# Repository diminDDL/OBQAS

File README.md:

# OBQAS
Open Battery Quantification and Analysis System

A high efficiency high power imax alternative.

Features include:

* up to 5 Li-ion cells (22 Vout max)

Supported battery types:
* Li-ion (with balancing)
* Ni-mh
* Ni-cd
* Pb
* More...

Ratings:
* Maximum output voltage - 22V
* Maximum charging current - 5A
* Maximum charging power: ~100W

Discharge:
* Maximum input voltage - 22V
* Maximum discharging current - 3A (up to 5A with a better MOSFET)
* Maximum discharging power: ~75W

Input voltage:
12-24V

Topology:
buck-boost synchronous (TPS55288)

Additional features:
20x4 display with encoder
USB-C for data logging and remote control/outputs 5V 1A
SD card holds configuration parameters/standalone data logging
Thermocopule for battery monitoring
ESP32 - WiFI/BLE

### Pictures

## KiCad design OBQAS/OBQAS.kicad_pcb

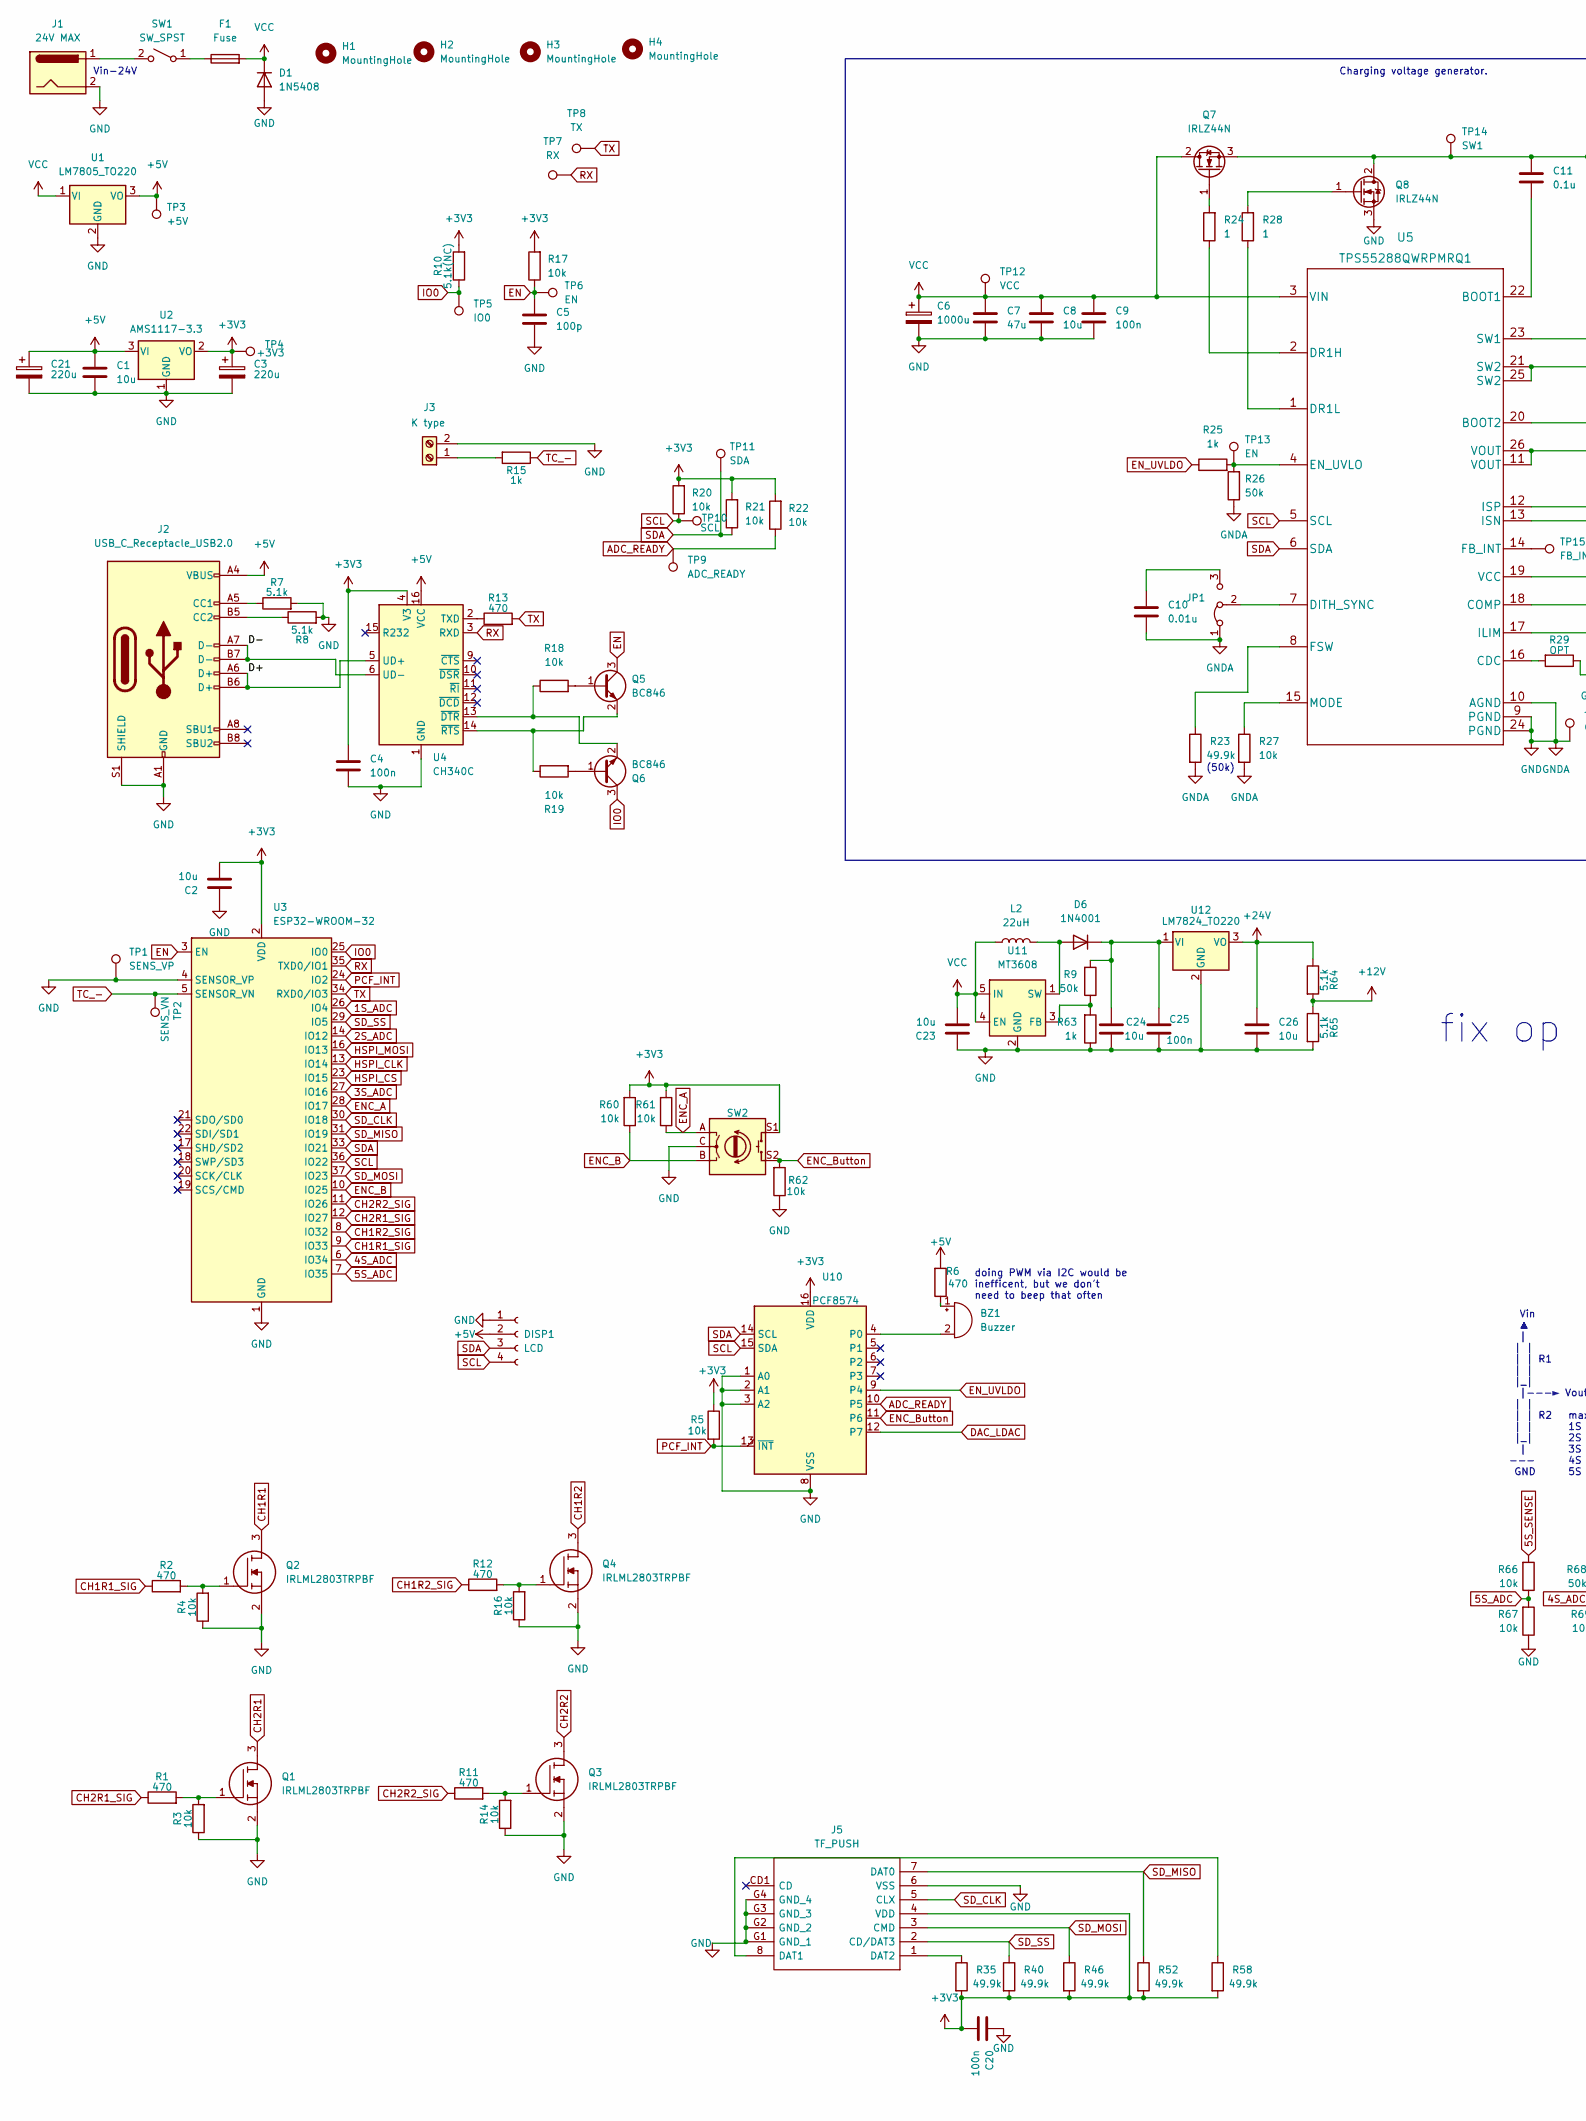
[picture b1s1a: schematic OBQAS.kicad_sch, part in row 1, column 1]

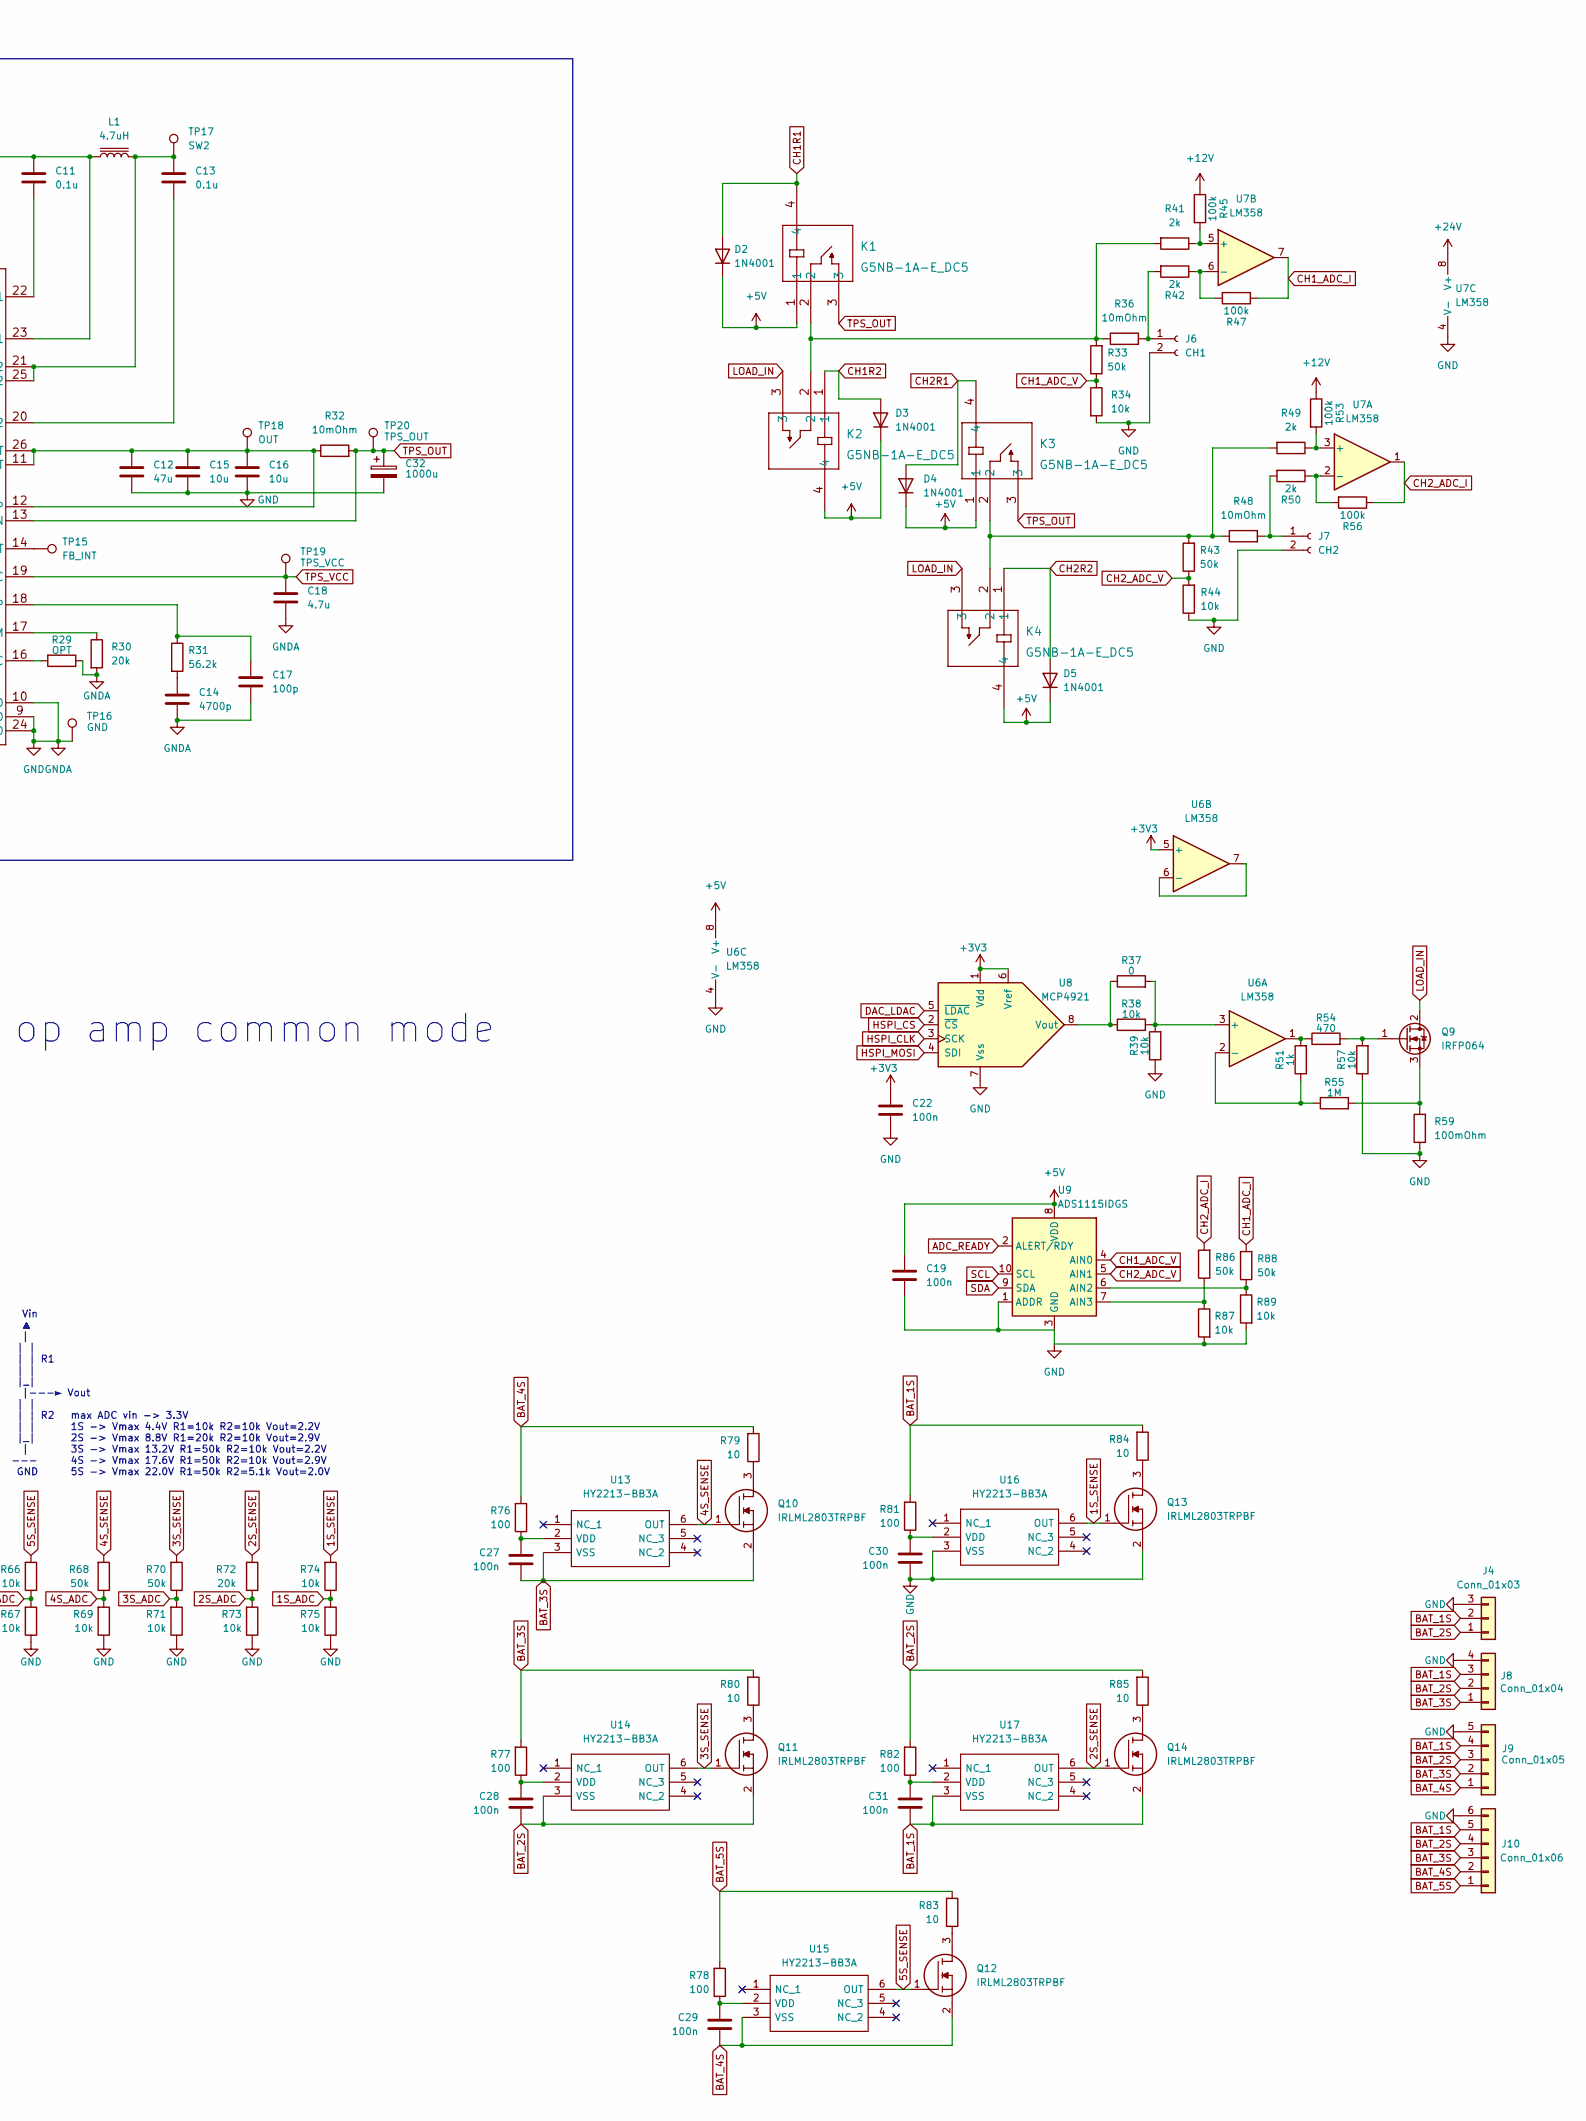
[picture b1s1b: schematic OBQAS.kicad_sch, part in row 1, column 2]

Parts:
BZ1: Buzzer; Buzzer_12x9.5RM7.6
C1, C2, C8, C15, C16, C23, C24, C26: 10u; C_1206_3216Metric_Pad1.33x1.80mm_HandSolder
C3, C21: 220u; CP_Elec_6.3x9.9
C4, C9, C19, C20, C22, C25, C27, C28, C29, C30, C31: 100n; C_0805_2012Metric_Pad1.18x1.45mm_HandSolder
C5, C17: 100p; C_0805_2012Metric_Pad1.18x1.45mm_HandSolder
C6: 1000u; CP_Elec_10x10
C7: 47u; CP_Elec_8x6.9
C10: 0.01u; C_0805_2012Metric_Pad1.18x1.45mm_HandSolder
C11, C13: 0.1u; C_0805_2012Metric_Pad1.18x1.45mm_HandSolder
C12: 47u; C_1210_3225Metric_Pad1.33x2.70mm_HandSolder
C14: 4700p; C_0805_2012Metric_Pad1.18x1.45mm_HandSolder
C18: 4.7u; C_1206_3216Metric_Pad1.33x1.80mm_HandSolder
C32: 1000u; CP_Radial_D10.0mm_P5.00mm
D1: 1N5408; D_DO-201AD_P15.24mm_Horizontal
D2, D3, D4, D5, D6: 1N4001; D_SOD-123
DISP1: LCD; LCD-20x4
F1: Fuse; Fuse_Blade_ATO_directSolder
H1, H2, H3, H4: MountingHole; MountingHole_3.2mm_M3
J1: 24V MAX; AMASS_XT60-F_1x02_P7.20mm_Vertical
J2: USB_C_Receptacle_USB2.0; USB_C_Receptacle_Palconn_UTC16-G
J3: K type; TerminalBlock_Altech_AK300-2_P5.00mm
J4: Conn_01x03; JST_XH_B3B-XH-A_1x03_P2.50mm_Vertical
J5: TF_PUSH; TFPUSH; Manufacturer_Part_Number TF PUSH
J6: CH1; TerminalBlock_Altech_AK300-2_P5.00mm
J7: CH2; TerminalBlock_Altech_AK300-2_P5.00mm
J8: Conn_01x04; JST_XH_B4B-XH-A_1x04_P2.50mm_Vertical
J9: Conn_01x05; JST_XH_B5B-XH-A_1x05_P2.50mm_Vertical
J10: Conn_01x06; JST_XH_B6B-XH-A_1x06_P2.50mm_Vertical
JP1: Jumper_3_Bridged12; SolderJumper-3_P1.3mm_Bridged12_RoundedPad1.0x1.5mm
K1, K2, K3, K4: G5NB-1A-E_DC5; G5NB-1A-E DC5
L1: 4.7uH; L_Radial_D29.8mm_P29.30mm_Murata_1400series
L2: 22uH; L_6.3x6.3_H3
Q1, Q2, Q3, Q4, Q10, Q11, Q12, Q13, Q14: IRLML2803TRPBF; SOT-23; Manufacturer_Part_Number IRLML2803TRPBF; Mouser Part Number 942-IRLML2803TRPBF
Q5, Q6: BC846; SOT-23
Q7, Q8: IRLZ44N; TO-220F-3_Horizontal_TabUp
Q9: IRFP064; TO-247-3_Horizontal_TabUp
R1, R2, R6, R11, R12, R13, R54: 470; R_0805_2012Metric_Pad1.20x1.40mm_HandSolder
R3, R4, R5, R14, R16, R17, R18, R19, R20, R21, R22, R27, R34, R38, R39, R44, R57, R60, R61, R62, R66, R67, R69, R71, R73, R74, R75, R87, R89: 10k; R_0805_2012Metric_Pad1.20x1.40mm_HandSolder
R7, R8, R64, R65: 5.1k; R_0805_2012Metric_Pad1.20x1.40mm_HandSolder
R9, R26, R33, R43, R68, R70, R86, R88: 50k; R_0805_2012Metric_Pad1.20x1.40mm_HandSolder
R10: 5.1k(NC); R_0805_2012Metric_Pad1.20x1.40mm_HandSolder
R15, R25, R51, R63: 1k; R_0805_2012Metric_Pad1.20x1.40mm_HandSolder
R23, R35, R40, R46, R52, R58: 49.9k; R_0805_2012Metric_Pad1.20x1.40mm_HandSolder
R24, R28: 1; R_0805_2012Metric_Pad1.20x1.40mm_HandSolder
R29: OPT; R_0805_2012Metric_Pad1.20x1.40mm_HandSolder
R30, R72: 20k; R_0805_2012Metric_Pad1.20x1.40mm_HandSolder
R31: 56.2k; R_0805_2012Metric_Pad1.20x1.40mm_HandSolder
R32, R36, R48: 10mOhm; R_2512_6332Metric_Pad1.40x3.35mm_HandSolder
R37: 0; R_0805_2012Metric_Pad1.20x1.40mm_HandSolder
R41, R42, R49, R50: 2k; R_0805_2012Metric_Pad1.20x1.40mm_HandSolder
R45, R47, R53, R56: 100k; R_0805_2012Metric_Pad1.20x1.40mm_HandSolder
R55: 1M; R_0805_2012Metric_Pad1.20x1.40mm_HandSolder
R59: 100mOhm; R_Axial_Power_L20.0mm_W6.4mm_P30.48mm
R76, R77, R78, R81: 100; R_0805_2012Metric_Pad1.20x1.40mm_HandSolder
R79, R80, R83, R84, R85: 10; R_2512_6332Metric_Pad1.40x3.35mm_HandSolder
R82: 100; L_0805_2012Metric_Pad1.15x1.40mm_HandSolder
SW1: SW_SPST; TerminalBlock_Altech_AK300-2_P5.00mm
SW2: Enc; RotaryEncoder_Alps_EC11E-Switch_Vertical_H20mm_CircularMoun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
TP1: SENS_VP; TestPoint_Pad_D2.5mm
TP2: SENS_VN; TestPoint_Pad_D2.5mm
TP3: +5V; TestPoint_Pad_D2.5mm
TP4: +3V3; TestPoint_Pad_D2.5mm
TP5: IO0; TestPoint_Pad_D2.5mm
TP6, TP13: EN; TestPoint_Pad_D2.5mm
TP7: RX; TestPoint_Pad_D2.5mm
TP8: TX; TestPoint_Pad_D2.5mm
TP9: ADC_READY; TestPoint_Pad_D2.5mm
TP10: SCL; TestPoint_Pad_D2.5mm
TP11: SDA; TestPoint_Pad_D2.5mm
TP12: VCC; TestPoint_Pad_D2.5mm
TP14: SW1; TestPoint_Pad_D2.5mm
TP15: FB_INT; TestPoint_Pad_D1.0mm
TP16: GND; TestPoint_Pad_D2.5mm
TP17: SW2; TestPoint_Pad_D2.5mm
TP18: OUT; TestPoint_Pad_D2.5mm
TP19: TPS_VCC; TestPoint_Pad_D2.5mm
TP20: TPS_OUT; TestPoint_Pad_D2.5mm
U1: LM7805_TO220; TO-220-3_Vertical
U2: AMS1117-3.3; SOT-223-3_TabPin2
U3: ESP32-WROOM-32
U4: CH340C; SOIC-16_3.9x9.9mm_P1.27mm
U5: TPS55288QWRPMRQ1
U6, U7: LM358; SO-8_3.9x4.9mm_P1.27mm
U8: MCP4921; SO-8_3.9x4.9mm_P1.27mm
U9: ADS1115IDGS; TSSOP-10_3x3mm_P0.5mm
U10: PCF8574; SOIC-16W_7.5x10.3mm_P1.27mm
U11: MT3608; SOT-23-6
U12: LM7824_TO220; TO-220-3_Vertical
U13, U14, U15, U16, U17: HY2213-BB3A; SOT95P280X140-6N; Manufacturer_Part_Number HY2213-BB3A

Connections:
1S_ADC: R74.1, R75.2, U3.26 (IO4)
1S_SENSE: Q13.1, R74.2, U16.6 (OUT)
2S_ADC: R72.1, R73.2, U3.14 (IO12)
2S_SENSE: Q14.1, R72.2, U17.6 (OUT)
3S_ADC: R70.1, R71.2, U3.27 (IO16)
3S_SENSE: Q11.1, R70.2, U14.6 (OUT)
4S_ADC: R68.1, R69.2, U3.6 (IO34)
4S_SENSE: Q10.1, R68.2, U13.6 (OUT)
5S_ADC: R66.1, R67.2, U3.7 (IO35)
5S_SENSE: Q12.1, R66.2, U15.6 (OUT)
+3V3: C2.2, C3.1, C4.1, C20.2, C22.1, J5.4 (VDD), R5.1, R10.2, R17.2, R20.2, R21.2, R22.2, R35.2, R40.2, R46.2, R52.2, R58.2, R60.2, R61.2, SW2.S1, TP4.1, U2.2 (VO), U3.2 (VDD), U4.4 (V3), U6.5 (+), U8.1 (Vdd), U8.6 (Vref), U10.16 (VDD)
+5V: C1.1, C19.1, C21.1, D2.1 (K), D3.1 (K), D4.1 (K), D5.1 (K), DISP1.2, J2.A4 (VBUS), J2.A9 (VBUS), J2.B4 (VBUS), J2.B9 (VBUS), K1.1, K2.4, K3.1, K4.4, R6.2, TP3.1, U1.3 (VO), U2.3 (VI), U4.16 (VCC), U6.8 (V+), U9.8 (VDD)
+12V: R45.1, R53.1, R64.2, R65.1
+24V: C26.1, R64.1, U7.8 (V+), U12.3 (VO)
/D+: J2.A6 (D+), J2.B6 (D+), U4.5 (UD+)
/D-: J2.A7 (D-), J2.B7 (D-), U4.6 (UD-)
ADC_READY: R22.1, TP9.1, U9.2 (ALERT/RDY), U10.10 (P5)
BAT_1S: C31.2, J4.2, J8.3, J9.4, J10.5, Q14.2, R81.2, R84.2, U17.3 (VSS)
BAT_2S: C28.2, J4.1, J8.2, J9.3, J10.4, Q11.2, R82.2, R85.2, U14.3 (VSS)
BAT_3S: C27.2, J8.1, J9.2, J10.3, Q10.2, R77.2, R80.2, U13.3 (VSS)
BAT_4S: C29.2, J9.1, J10.2, Q12.2, R76.2, R79.2, U15.3 (VSS)
BAT_5S: J10.1, R78.2, R83.2
CH1R1: D2.2 (A), K1.4, Q2.3
CH1R1_SIG: R2.1, U3.9 (IO33)
CH1R2: D3.2 (A), K2.1, Q4.3
CH1R2_SIG: R12.1, U3.8 (IO32)
CH1_ADC_I: R47.1, R88.2, U7.7
CH1_ADC_V: R33.1, R34.1, U9.4 (AIN0)
CH2R1: D4.2 (A), K3.4, Q1.3
CH2R1_SIG: R1.1, U3.12 (IO27)
CH2R2: D5.2 (A), K4.1, Q3.3
CH2R2_SIG: R11.1, U3.11 (IO26)
CH2_ADC_I: R56.1, R86.2, U7.1
CH2_ADC_V: R43.1, R44.2, U9.5 (AIN1)
DAC_LDAC: U8.5 (~LDAC), U10.12 (P7)
EN: C5.1, Q5.3 (C), R17.1, TP6.1, U3.3 (EN)
ENC_A: R61.1, SW2.A, U3.28 (IO17)
ENC_B: R60.1, SW2.B, U3.10 (IO25)
ENC_Button: R62.2, SW2.S2, U10.11 (P6)
EN_UVLDO: R25.1, U10.9 (P4)
GND: C1.2, C2.1, C3.2, C4.2, C5.2, C6.2, C7.2, C8.2, C9.2, C10.2, C12.2, C14.2, C15.2, C16.2, C17.2, C18.2, C19.2, C20.1, C21.2, C22.2, C23.1, C24.2, C25.2, C26.2, C30.2, C32.2, D1.2 (A), DISP1.1, J1.2, J2.A1 (GND), J2.A12 (GND), J2.B1 (GND), J2.B12 (GND), J2.S1 (SHIELD), J3.2, J4.3, J5.6 (VSS), J5.G1 (GND_1), J5.G2 (GND_2), J5.G3 (GND_3), J5.G4 (GND_4), J6.2, J7.2, J8.4, J9.5, J10.6, JP1.1 (A), Q1.2, Q2.2, Q3.2, Q4.2, Q8.3 (S), Q13.2, R3.1, R4.1, R7.2, R8.2, R14.1, R16.1, R23.2, R26.1, R27.2, R29.1, R30.2, R34.2, R39.1, R44.1, R57.1, R59.1, R62.1, R63.1, R65.2, R67.1, R69.1, R71.1, R73.1, R75.1, R87.2, R89.2, SW2.C, TP1.1, TP16.1, U1.2 (GND), U2.1 (GND), U3.1 (GND), U3.4 (SENSOR_VP), U3.15 (GND), U3.38 (GND), U3.39 (GND), U4.1 (GND), U5.9 (PGND), U5.10 (AGND), U5.24 (PGND), U6.4 (V-), U7.4 (V-), U8.7 (Vss), U9.1 (ADDR), U9.3 (GND), U10.1 (A0), U10.2 (A1), U10.3 (A2), U10.8 (VSS), U11.2 (GND), U12.2 (GND), U16.3 (VSS)
HSPI_CLK: U3.13 (IO14), U8.3 (SCK)
HSPI_CS: U3.23 (IO15), U8.2 (~CS)
HSPI_MOSI: U3.16 (IO13), U8.4 (SDI)
IO0: Q6.3 (C), R10.1, TP5.1, U3.25 (IO0)
LOAD_IN: K2.3, K4.3, Q9.2 (D)
unnamed: BZ1.1 (-), R6.1
unnamed: BZ1.2 (+), U10.4 (P0)
unnamed: C10.1, JP1.3 (B)
unnamed: C11.1, L1.1, Q7.3 (S), Q8.2 (D), TP14.1, U5.23 (SW1)
unnamed: C11.2, U5.22 (BOOT1)
unnamed: C12.1, C15.1, C16.1, R32.1, TP18.1, U5.11 (VOUT), U5.12 (ISP), U5.26 (VOUT)
unnamed: C13.1, L1.2, TP17.1, U5.21 (SW2), U5.25 (SW2)
unnamed: C13.2, U5.20 (BOOT2)
unnamed: C14.1, R31.2
unnamed: C17.1, R31.1, U5.18 (COMP)
unnamed: C24.1, C25.1, D6.1 (K), R9.2, U12.1 (VI)
unnamed: C27.1, R76.1, U13.2 (VDD)
unnamed: C28.1, R77.1, U14.2 (VDD)
unnamed: C29.1, R78.1, U15.2 (VDD)
unnamed: C30.1, R81.1, U16.2 (VDD)
unnamed: C31.1, R82.1, U17.2 (VDD)
unnamed: D6.2 (A), L2.2, U11.1 (SW)
unnamed: F1.1, SW1.1 (A)
unnamed: J1.1, SW1.2 (B)
unnamed: J2.A5 (CC1), R7.1
unnamed: J2.B5 (CC2), R8.1
unnamed: J3.1, R15.2
unnamed: J5.1 (DAT2), R35.1
unnamed: J5.8 (DAT1), R58.1
unnamed: J6.1, R36.2, R42.2
unnamed: J7.1, R48.2, R50.2
unnamed: JP1.2 (C), U5.7 (DITH_SYNC)
unnamed: K1.2, K2.2, R33.2, R36.1, R41.2
unnamed: K3.2, K4.2, R43.2, R48.1, R49.2
unnamed: Q1.1, R1.2, R3.2
unnamed: Q2.1, R2.2, R4.2
unnamed: Q3.1, R11.2, R14.2
unnamed: Q4.1, R12.2, R16.2
unnamed: Q5.1 (B), R18.2
unnamed: Q5.2 (E), R19.1, U4.14 (~RTS)
unnamed: Q6.1 (B), R19.2
unnamed: Q6.2 (E), R18.1, U4.13 (~DTR)
unnamed: Q7.1 (G), R24.2
unnamed: Q8.1 (G), R28.2
unnamed: Q9.1 (G), R54.2, R57.2
unnamed: Q9.3 (S), R55.2, R59.2
unnamed: Q10.3, R79.1
unnamed: Q11.3, R80.1
unnamed: Q12.3, R83.1
unnamed: Q13.3, R84.1
unnamed: Q14.3, R85.1
unnamed: R13.1, U4.2 (TXD)
unnamed: R23.1, U5.8 (FSW)
unnamed: R24.1, U5.2 (DR1H)
unnamed: R25.2, R26.2, TP13.1, U5.4 (EN_UVLO)
unnamed: R27.1, U5.15 (MODE)
unnamed: R28.1, U5.1 (DR1L)
unnamed: R29.2, U5.16 (CDC)
unnamed: R30.1, U5.17 (ILIM)
unnamed: R37.1, R38.1, U8.8 (Vout)
unnamed: R37.2, R38.2, R39.2, U6.3 (+)
unnamed: R41.1, R45.2, U7.5 (+)
unnamed: R42.1, R47.2, U7.6 (-)
unnamed: R49.1, R53.2, U7.3 (+)
unnamed: R50.1, R56.2, U7.2 (-)
unnamed: R51.1, R55.1, U6.2 (-)
unnamed: R51.2, R54.1, U6.1
unnamed: R9.1, R63.2, U11.3 (FB)
unnamed: R86.1, R87.1, U9.7 (AIN3)
unnamed: R88.1, R89.1, U9.6 (AIN2)
unnamed: TP15.1, U5.14 (FB_INT)
unnamed: U6.6 (-), U6.7
PCF_INT: R5.2, U3.24 (IO2), U10.13 (~INT)
RX: TP7.1, U3.35 (TXD0/IO1), U4.3 (RXD)
SCL: DISP1.4, R20.1, TP10.1, U3.36 (IO22), U5.5 (SCL), U9.10 (SCL), U10.15 (SDA)
SDA: DISP1.3, R21.1, TP11.1, U3.33 (IO21), U5.6 (SDA), U9.9 (SDA), U10.14 (SCL)
SD_CLK: J5.5 (CLX), U3.30 (IO18)
SD_MISO: J5.7 (DAT0), R52.1, U3.31 (IO19)
SD_MOSI: J5.3 (CMD), R46.1, U3.37 (IO23)
SD_SS: J5.2 (CD/DAT3), R40.1, U3.29 (IO5)
TC_-: R15.1, TP2.1, U3.5 (SENSOR_VN)
TPS_OUT: C32.1, K1.3, K3.3, R32.2, TP20.1, U5.13 (ISN)
TPS_VCC: C18.1, TP19.1, U5.19 (VCC)
TX: R13.2, TP8.1, U3.34 (RXD0/IO3)
VCC: C6.1, C7.1, C8.1, C9.1, C23.2, D1.1 (K), F1.2, L2.1, Q7.2 (D), TP12.1, U1.1 (VI), U5.3 (VIN), U11.4 (EN), U11.5 (IN)

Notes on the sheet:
max ADC vin -> 3.3V 1S -> Vmax 4.4V R1=10k R2=10k Vout=2.2V 2S -> Vmax 8.8V R1=20k R2=10k Vout=2.9V 3S -> Vmax 13.2V R1=50k R2=10k Vout=2.2V 4S -> Vmax 17.6V R1=50k R2=10k Vout=2.9V 5S -> Vmax 22.0V R1=50k R2=5.1k Vout=2.0V
(50k)
Vin-24V
Charging voltage generator.
Vin ▲ | | | | | R1 | | |_| |---► Vout | | | | R2 | | |_| | --- GND
fix op amp common mode
doing PWM via I2C would be inefficent, but we don't need to beep that often

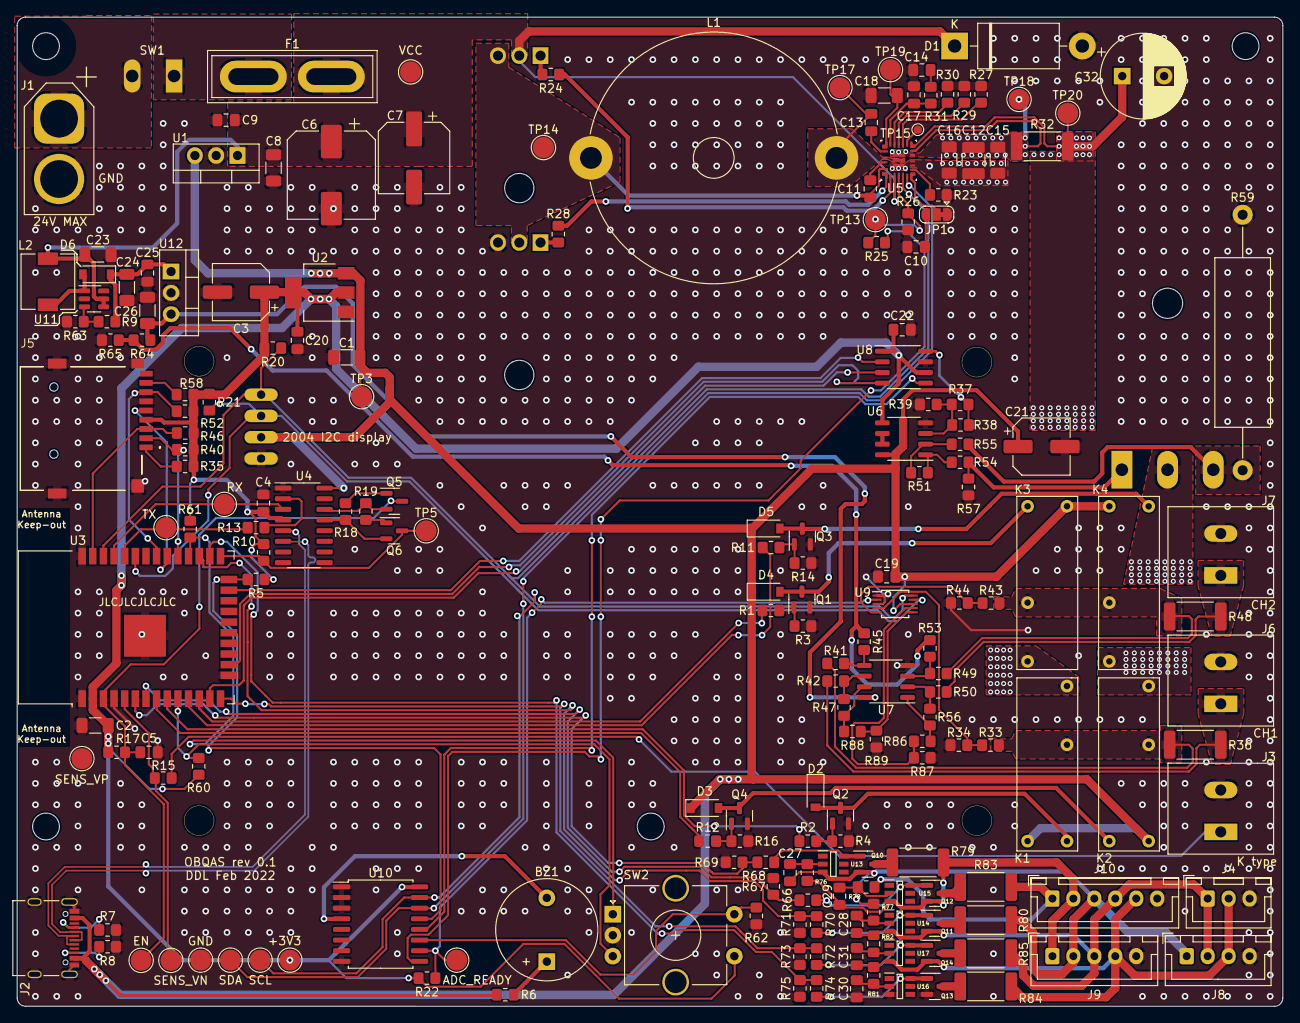
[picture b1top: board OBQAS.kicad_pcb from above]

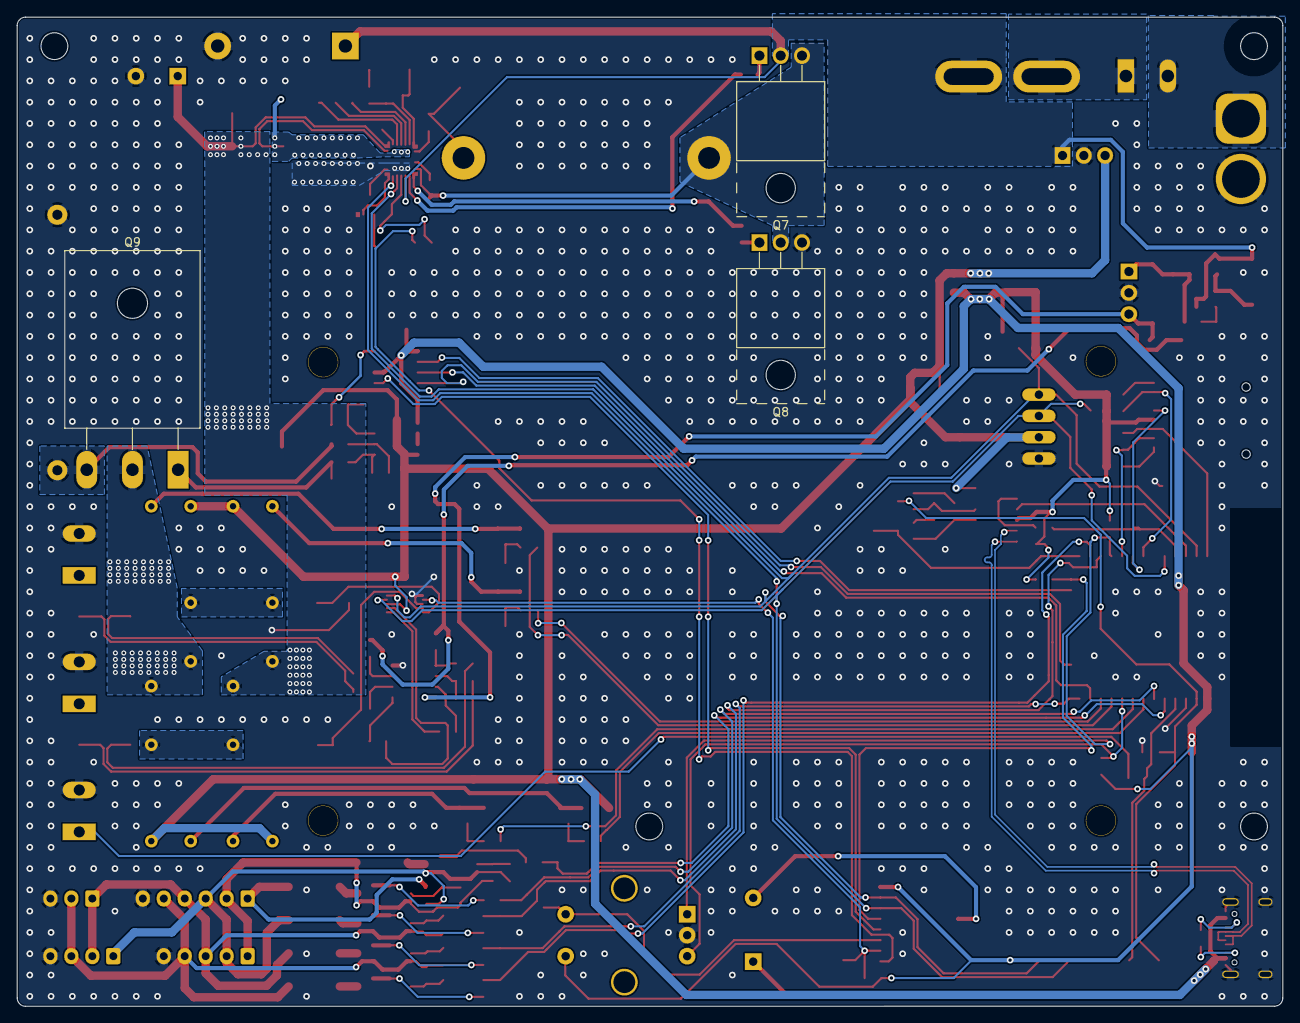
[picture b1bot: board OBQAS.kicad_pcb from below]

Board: 2 copper layers, 151.0 x 118.0 mm, 204 parts (3 on the bottom side), 126 nets.

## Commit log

2022-01-21 intial schematic design
2022-01-24 continued schematic editing
2022-01-25 Finished schematic
2022-01-25 changed SD card
2022-01-25 added encoder and assigned some footprints
2022-01-26 beginning of PCB layout
2022-01-27 inital routing complete
2022-01-27 finished layout, doing silkscreen adjustment
2022-01-27 additional schematic changes to accommodate balancing
2022-02-01 updated schematic with balancing circuit
2022-02-01 finished routing of the new circuit
2022-02-02 final PCB
2022-02-02 smal tweaks to the PCB
2022-02-02 added gerbers
2022-05-10 minor changes
2022-06-18 updated PDF
2022-12-21 added 3D render
